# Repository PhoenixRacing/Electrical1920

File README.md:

# Electrical1920
Firmware, software, and component design of sensing and computer systems for the 2019-2020 season

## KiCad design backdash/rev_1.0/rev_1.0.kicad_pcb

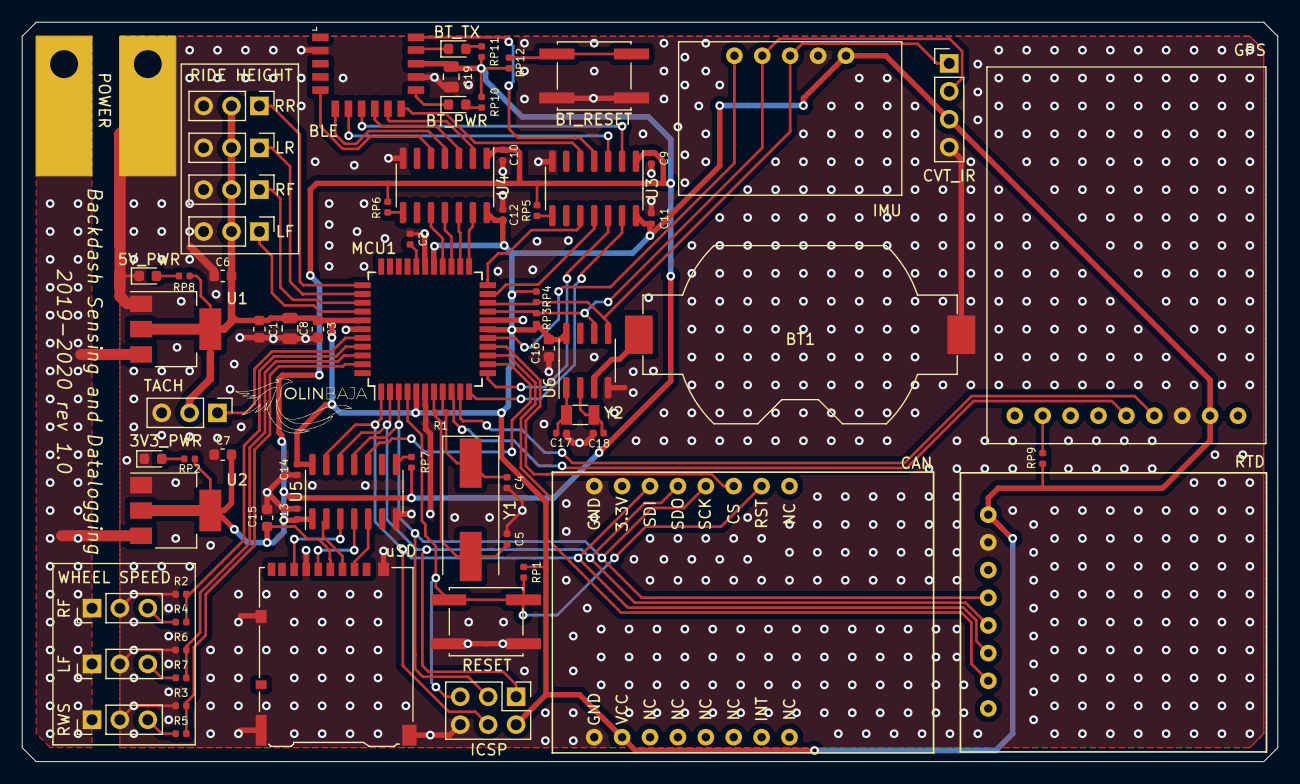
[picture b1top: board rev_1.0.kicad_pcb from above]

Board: 2 copper layers, 114.3 x 67.3 mm, 71 parts (0 on the bottom side), 64 nets.

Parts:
3V3_PWR, 5V_PWR: Green; LED_0603_1608Metric
BLE: RN4871-V/RM118; Microchip_RN4871
BT1: 3V Coin Cell; BatteryHolder_Keystone_1058_1x2032
BT_PWR: BT_PLED; LED_0603_1608Metric
BT_RESET: BT_RST; SW_SPST_EVQQ2
BT_TX: BT_TX_LED; LED_0603_1608Metric
C1, C3, C6, C7, C15, C16: 1uF; C_0603_1608Metric
C2, C9, C10, C11, C12, C13, C14: 0.1uF; C_0402_1005Metric
C4, C5: 20pF; C_0402_1005Metric
C8: 4.7uF_16V; C_0805_2012Metric
C17, C18: 18pF; C_0402_1005Metric
C19: 10uF; C_0805_2012Metric
CAN: SPI_CAN_BREAKOUT; CAN_Module
CVT_IR: CVT_IR; PinHeader_1x04_P2.54mm_Vertical
GPS: Ulti_GPS_v3; UltiGPSv3
ICSP: ICSP; PinHeader_2x03_P2.54mm_Vertical
IMU: IMU_bout; 6dof_MPU6050
J2: RF; PinHeader_1x03_P2.54mm_Vertical
J3: RWS; PinHeader_1x03_P2.54mm_Vertical
J5: LF; PinHeader_1x03_P2.54mm_Vertical
LF: LF_rh; PinHeader_1x03_P2.54mm_Vertical
LR: LR_rh; PinHeader_1x03_P2.54mm_Vertical
MCU1: ATmega1284-AU; TQFP-44_10x10mm_P0.8mm
POWER: Vsupply; Power
R1: 1M; R_0402_1005Metric
R2, R3, R6: 4.7k; R_0402_1005Metric
R4, R5, R7: 1k; R_0402_1005Metric
RESET: BT_RST; SW_SPST_EVQQ2
RF: RF_rh; PinHeader_1x03_P2.54mm_Vertical
RP1, RP9, RP12: 10k; R_0402_1005Metric
RP2, RP5, RP6, RP7, RP8, RP10, RP11: 1k; R_0402_1005Metric
RP3, RP4: 4.7k; R_0402_1005Metric
RR: RR_rh; PinHeader_1x03_P2.54mm_Vertical
RTD: MAX31865; RTD
TACH: Tach; PinHeader_1x03_P2.54mm_Vertical
U1: LM1117-5.0; SOT-223
U2: LM1117-3.3; SOT-223
U3, U4, U5: TXB0104D; SOIC-14_3.9x8.7mm_P1.27mm
U6: MCP7940N-xSN; SOIC-8_3.9x4.9mm_P1.27mm
Y1: 16MHz; Crystal_SMD_HC49-SD
Y2: 32.768 kHz; Crystal_SMD_3215-2Pin_3.2x1.5mm
uSD: Micro_SD_Card_Det_Hirose_DM3AT; microSD_HC_Hirose_DM3AT-SF-PEJM5

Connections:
+3V3: BLE.14, C7.1, C9.1, C10.1, C13.1, C15.1, C19.1, RP2.2, RP5.1, RP6.1, RP7.1, RP10.2, RP11.2, RP12.1, U2.2, U2.4, U3.1, U4.1, U5.1, uSD.4
+5V: C1.1, C3.1, C6.1, C8.1, C11.2, C12.2, C14.2, C16.1, CAN.15, CVT_IR.3, GPS.8, ICSP.2, IMU.1, LF.2, LR.2, MCU1.5, MCU1.17, MCU1.27, MCU1.38, RF.2, RP1.1, RP3.1, RP4.1, RP8.2, RP9.2, RR.2, RTD.1, TACH.2, U1.2, U1.4, U3.14, U4.14, U5.14, U6.8
+7.5V: J2.1, J3.1, J5.1, POWER.1, U1.3, U2.3
/A0: LF.1, MCU1.37
/A1: MCU1.36, RF.1
/A2: LR.1, MCU1.35
/A3: MCU1.34, RR.1
/BT_RST: BLE.10, U4.2
/BlueTooth/P0_2: BLE.12, BT_PWR.1
/BlueTooth/P2_7: BLE.15, BT_TX.1
/BlueTooth/RST_BT: BT_RESET.2, RP12.2
/CS_3V3: U5.5, uSD.2
/MISO: CAN.4, ICSP.1, MCU1.2, RTD.5, U5.12
/MISO_3V3: U5.3, uSD.7
/MOSI: CAN.3, ICSP.4, MCU1.1, RTD.6, U5.13
/MOSI_3V3: U5.2, uSD.3
/P0_0: BLE.11, U3.5
/P1_6: BLE.6, U4.4
/P1_7: BLE.5, U4.5
/P2_0: BLE.16, U3.4
/P3_6: BLE.9, U4.3
/PCINT8: MCU1.40, TACH.1
/PCINT9: MCU1.41, R2.2, R4.2
/PCINT10: MCU1.42, R6.2, R7.2
/PCINT11: MCU1.43, R3.2, R5.2
/PCINT18: MCU1.21, U3.11
/PCINT19: MCU1.22, U3.10
/PCINT20: MCU1.23, U4.13
/PCINT21: MCU1.24, U4.12
/PCINT22: MCU1.25, U4.11
/PCINT23: MCU1.26, U4.10
/PCINT28: MCU1.13, U5.10
/PCINT29: MCU1.14, RTD.7
/PCINT30: CAN.6, MCU1.15
/PCINT31: IMU.5, MCU1.16
/RESET: CAN.7, ICSP.5, MCU1.4, RESET.2, RP1.2
/RX0: GPS.5, MCU1.9
/RX1: MCU1.11, U3.13
/RX_3V3: BLE.7, U3.3
/SCK: CAN.5, ICSP.3, MCU1.3, RTD.4, U5.11
/SCK_3V3: U5.4, uSD.5
/SCL: CVT_IR.2, IMU.4, MCU1.19, RP3.2, U6.6
/SDA: CVT_IR.1, IMU.3, MCU1.20, RP4.2, U6.5
/TX0: GPS.6, MCU1.10
/TX1: MCU1.12, U3.12
/TX_3V3: BLE.8, U3.2
/XTAL1: C4.2, MCU1.8, R1.1, Y1.1
/XTAL2: C5.2, MCU1.7, R1.2, Y1.2
GND: 3V3_PWR.1, 5V_PWR.1, BLE.2, BLE.13, BT1.2, BT_RESET.1, C1.2, C2.1, C3.2, C4.1, C5.1, C6.2, C7.2, C8.2, C9.2, C10.2, C11.1, C12.1, C13.2, C14.1, C15.2, C16.2, C17.1, C18.2, C19.2, CAN.1, CAN.16, CVT_IR.4, GPS.7, ICSP.6, IMU.2, J2.2, J3.2, J5.2, LF.3, LR.3, MCU1.6, MCU1.18, MCU1.28, MCU1.39, POWER.2, R2.1, R3.1, R6.1, RESET.1, RF.3, RR.3, RTD.2, TACH.3, U1.1, U2.1, U3.7, U4.7, U5.7, U6.4, uSD.6, uSD.11
unnamed: BT1.1, U6.3
unnamed: C2.2, MCU1.29
unnamed: C17.2, U6.1, Y2.1
unnamed: C18.1, U6.2, Y2.2
unnamed: BT_PWR.2, RP10.1
unnamed: BT_TX.2, RP11.1
unnamed: J2.3, R4.1
unnamed: J3.3, R5.1
unnamed: J5.3, R7.1
unnamed: GPS.2, RP9.1
unnamed: 3V3_PWR.2, RP2.1
unnamed: 5V_PWR.2, RP8.1
unnamed: RP5.2, U3.8
unnamed: RP6.2, U4.8
unnamed: RP7.2, U5.8

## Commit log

2019-09-19 Annotated Schematic
2019-10-01 Pushing Library
2019-10-04 added sensor logic subsheets
2019-11-14 begin routing
2019-11-18 added stitching vias
2019-11-18 beep boop
2019-11-20 passes DRC, looks pretty
2019-12-18 ready to go
2019-12-18 ready
